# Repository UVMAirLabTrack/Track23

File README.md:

# UVM SEED 2023 Track
 
## Repository for code and setup files associated with the 2023 UVM SEED Project for an urban track for autonomous cars

## File Structure

### A. Documentation
Look in here to find the detailed instructions on how to build and run the track system. As well as more in depth information as to the system's function

- 
- 
- 
- 

### 3D modelling

Under this folder are organized locations for all the .stl files used to create the various printed elements. 

### Interactive Elements

Here you will find the Arduino IDE code files used for the ESP32 interactive element network.
Additionally Kicad format PCB's and schematics are located here.
The receiver for each interactive element utilizes the same PCB, with 4 RJ45 connectors and a single ESP32 Dev Module with 38 pins (WROOM- D or E)
The only change is which code file is flashed. 

Some previous versions utilizing pure serial connections have been left for adapability. The latest track build utilizes:

1. Stoplight
    - ESPnow_4way_4int.ino  
    - ESP_now_3Way.ino
2. Train Crossing
    - ESPNowTrain_Complete.ino
3. Sender
    - ESPnowSender.ino

With the sender node being connected via serial to the computer controlling the track, In this case a Raspberry Pi 4B 8GB model.

### CoreRaspbery 
is the ROS2 Workspace,

at present the code is designed to build into a Humble distro, however in testing the code can also be built for a Foxy distro.

### Setup Files 
contains some basic files to aid in deploying the Raspberry Pi track computer

### Car commands 
is a curated list of the terminal commands needed to operate specific functions of the Yahboom R2 car
Also contained within are some quality of life improvements to the deployment of the docker environment on the car, just some simple .sh files.

### Other Code

A series of files not directly part of the track functionality. Mostly a series of HSV decoders and Webcam Capture files 

### files not in a folder

the Dockerfiles in the main directory are intended to build a docker container to run all the ROS code, this is not intended for deployment on the PI as of this moment, instead it is intended as a complete package for the vizualizer node(s). At present, windows communication via WiFi is not functional due to additional networking constraints.

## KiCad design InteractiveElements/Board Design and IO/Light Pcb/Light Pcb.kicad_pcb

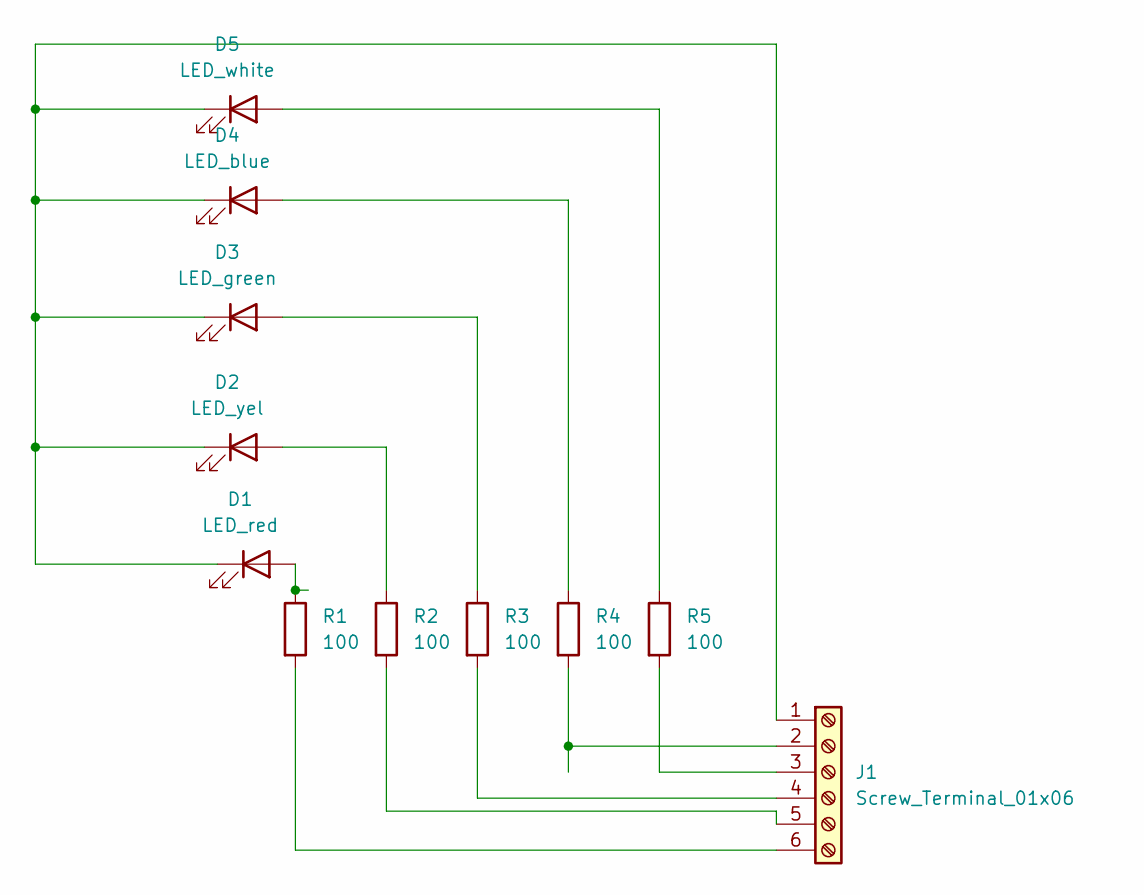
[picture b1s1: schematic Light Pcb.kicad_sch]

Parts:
D1: LED_red; LED_D5.0mm_Clear
D2: LED_yel; LED_D5.0mm_Clear
D3: LED_green; LED_D5.0mm_Clear
D4: LED_blue; LED_D5.0mm_Clear
D5: LED_white; LED_D5.0mm_Clear
J1: Screw_Terminal_01x06; PinHeader_1x06_P2.54mm_Vertical
R1, R2, R3, R4, R5: 100; R_Axial_DIN0204_L3.6mm_D1.6mm_P5.08mm_Horizontal

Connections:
unnamed: D1.2 (A), R1.1
unnamed: D1.1 (K), D2.1 (K), D3.1 (K), D4.1 (K), D5.1 (K), J1.1
unnamed: D2.2 (A), R2.1
unnamed: D3.2 (A), R3.1
unnamed: D4.2 (A), R4.1
unnamed: D5.2 (A), R5.1
unnamed: J1.2, R4.2
unnamed: J1.3, R5.2
unnamed: J1.4, R3.2
unnamed: J1.5, R2.2
unnamed: J1.6, R1.2

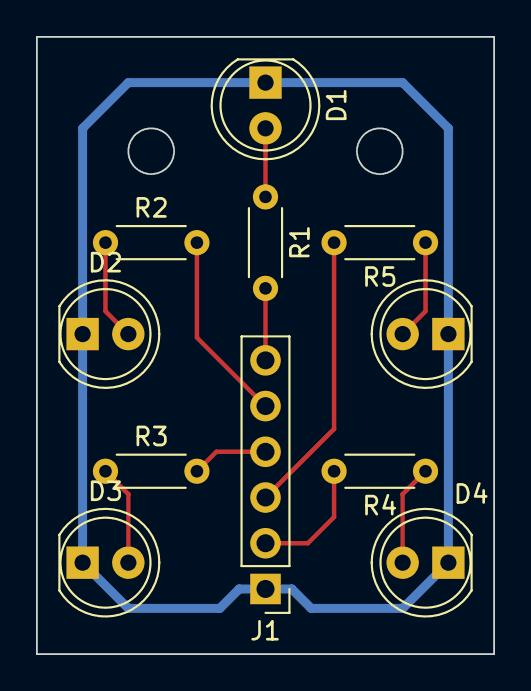
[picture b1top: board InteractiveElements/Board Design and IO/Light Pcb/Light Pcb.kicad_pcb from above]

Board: 2 copper layers, 25.4 x 34.3 mm, 11 parts (0 on the bottom side), 11 nets.

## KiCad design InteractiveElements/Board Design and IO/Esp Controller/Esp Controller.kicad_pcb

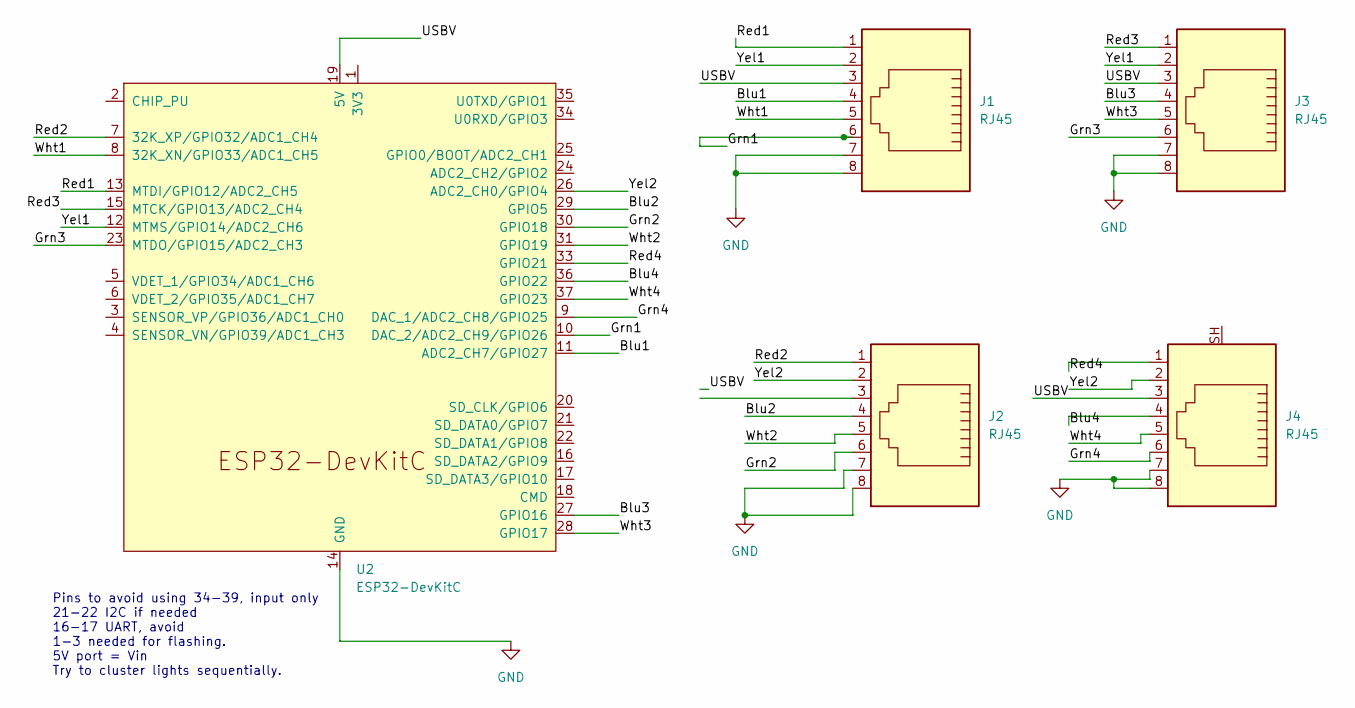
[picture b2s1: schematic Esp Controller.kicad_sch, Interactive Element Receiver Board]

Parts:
J1, J2, J3, J4: RJ45; RJ45_Amphenol_54602-x08_Horizontal
U2: ESP32-DevKitC

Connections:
/Blu1: J1.4, U2.11 (ADC2_CH7/GPIO27)
/Blu2: J2.4, U2.29 (GPIO5)
/Blu3: J3.4, U2.27 (GPIO16)
/Blu4: J4.4, U2.36 (GPIO22)
/Grn1: J1.6, U2.10 (DAC_2/ADC2_CH9/GPIO26)
/Grn2: J2.6, U2.30 (GPIO18)
/Grn3: J3.6, U2.23 (MTDO/GPIO15/ADC2_CH3)
/Grn4: J4.6, U2.9 (DAC_1/ADC2_CH8/GPIO25)
/Red1: J1.1, U2.13 (MTDI/GPIO12/ADC2_CH5)
/Red2: J2.1, U2.7 (32K_XP/GPIO32/ADC1_CH4)
/Red3: J3.1, U2.15 (MTCK/GPIO13/ADC2_CH4)
/Red4: J4.1, U2.33 (GPIO21)
/USBV: J1.3, J2.3, J3.3, J4.3, U2.19 (5V)
/Wht1: J1.5, U2.8 (32K_XN/GPIO33/ADC1_CH5)
/Wht2: J2.5, U2.31 (GPIO19)
/Wht3: J3.5, U2.28 (GPIO17)
/Wht4: J4.5, U2.37 (GPIO23)
/Yel1: J1.2, J3.2, U2.12 (MTMS/GPIO14/ADC2_CH6)
/Yel2: J2.2, J4.2, U2.26 (ADC2_CH0/GPIO4)
GND: J1.7, J1.8, J2.7, J2.8, J3.7, J3.8, J4.7, J4.8, U2.14 (GND), U2.32 (GND), U2.38 (GND)

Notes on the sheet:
Pins to avoid using 34-39, input only 21-22 I2C if needed 16-17 UART, avoid 1-3 needed for flashing. 5V port = Vin Try to cluster lights sequentially.

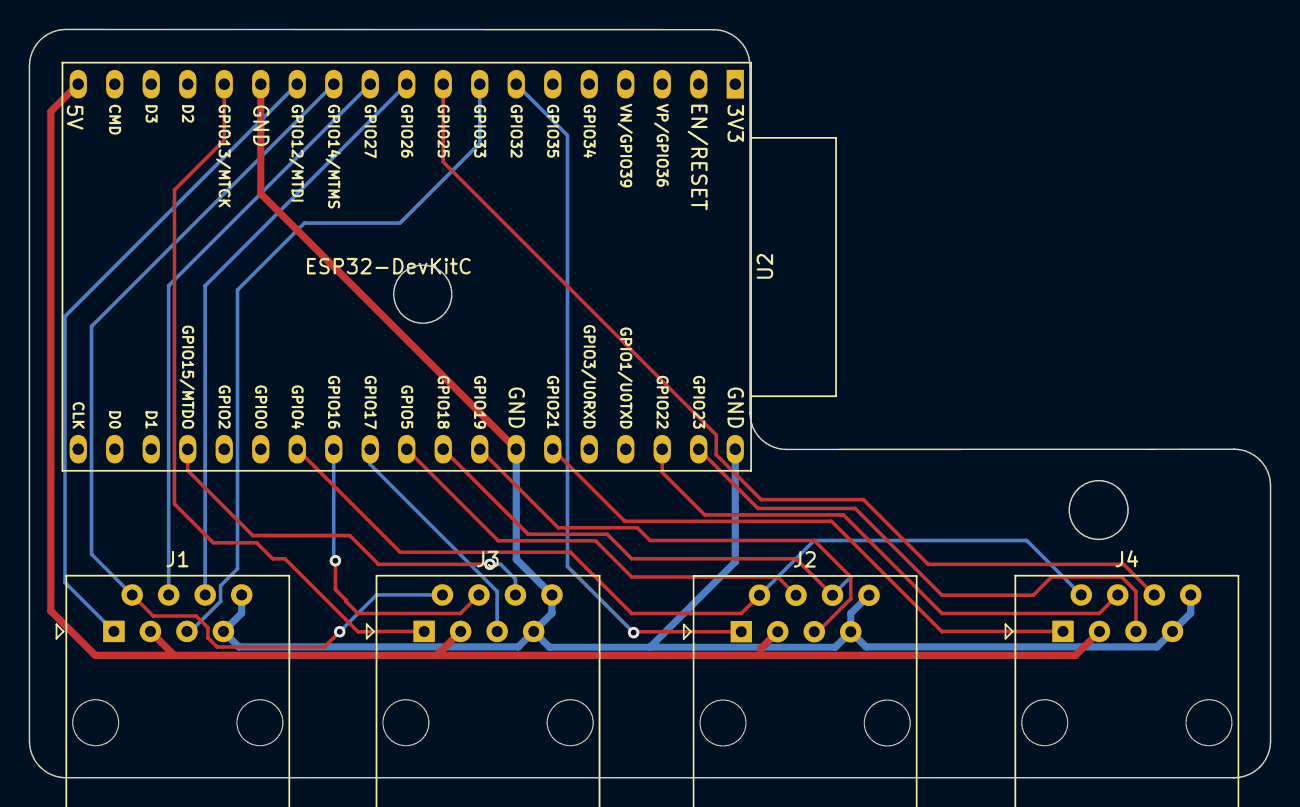
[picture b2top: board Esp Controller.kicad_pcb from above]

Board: 2 copper layers, 86.4 x 52.1 mm, 5 parts (0 on the bottom side), 20 nets.

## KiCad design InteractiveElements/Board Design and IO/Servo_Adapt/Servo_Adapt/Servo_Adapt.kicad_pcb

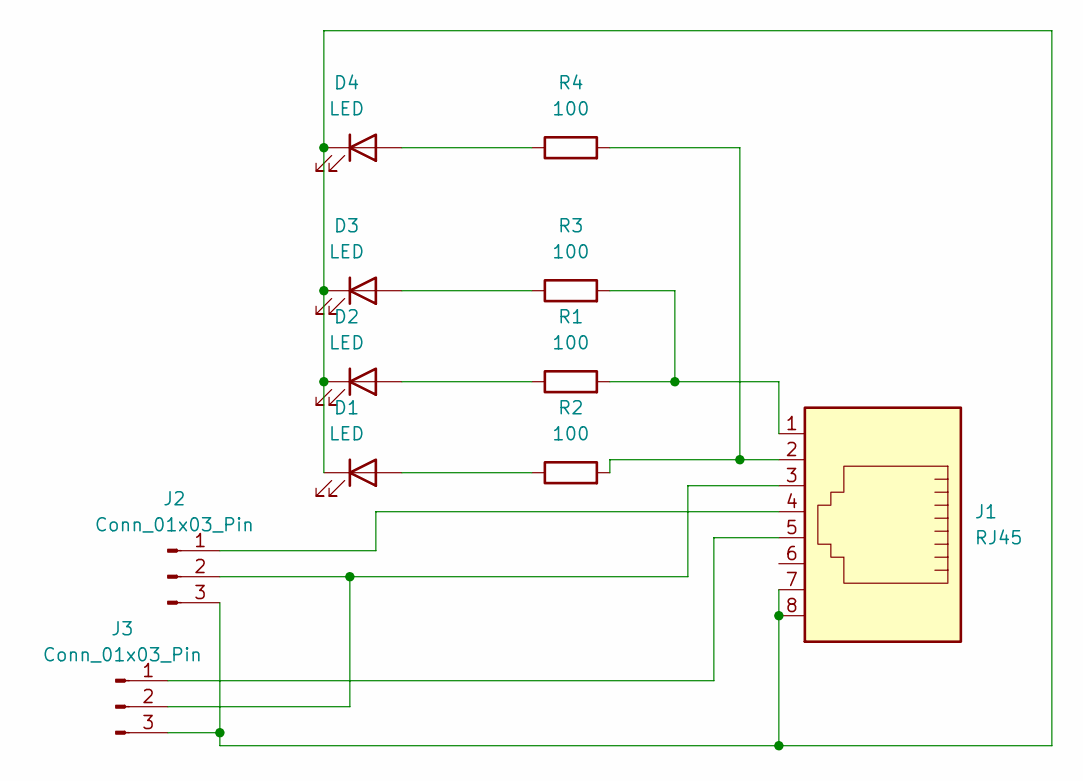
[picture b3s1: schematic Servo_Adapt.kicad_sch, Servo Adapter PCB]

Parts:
D1, D2, D3, D4: LED; LED_D5.0mm
J1: RJ45; RJ45_Amphenol_54602-x08_Horizontal
J2, J3: Conn_01x03_Pin; PinHeader_1x03_P2.54mm_Vertical
R1, R2, R3, R4: 100; R_Axial_DIN0207_L6.3mm_D2.5mm_P10.16mm_Horizontal

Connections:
unnamed: D1.2 (A), R2.1
unnamed: D1.1 (K), D2.1 (K), D3.1 (K), D4.1 (K), J1.7, J1.8, J2.3, J3.3
unnamed: D2.2 (A), R1.1
unnamed: D3.2 (A), R3.1
unnamed: D4.2 (A), R4.1
unnamed: J1.1, R1.2, R3.2
unnamed: J1.2, R2.2, R4.2
unnamed: J1.4, J2.1
unnamed: J1.3, J2.2, J3.2
unnamed: J1.5, J3.1

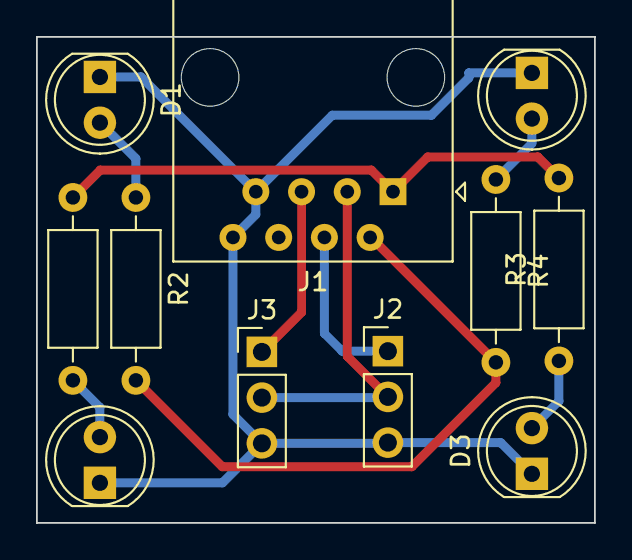
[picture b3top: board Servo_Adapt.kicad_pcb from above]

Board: 2 copper layers, 31.0 x 27.0 mm, 11 parts (0 on the bottom side), 10 nets.

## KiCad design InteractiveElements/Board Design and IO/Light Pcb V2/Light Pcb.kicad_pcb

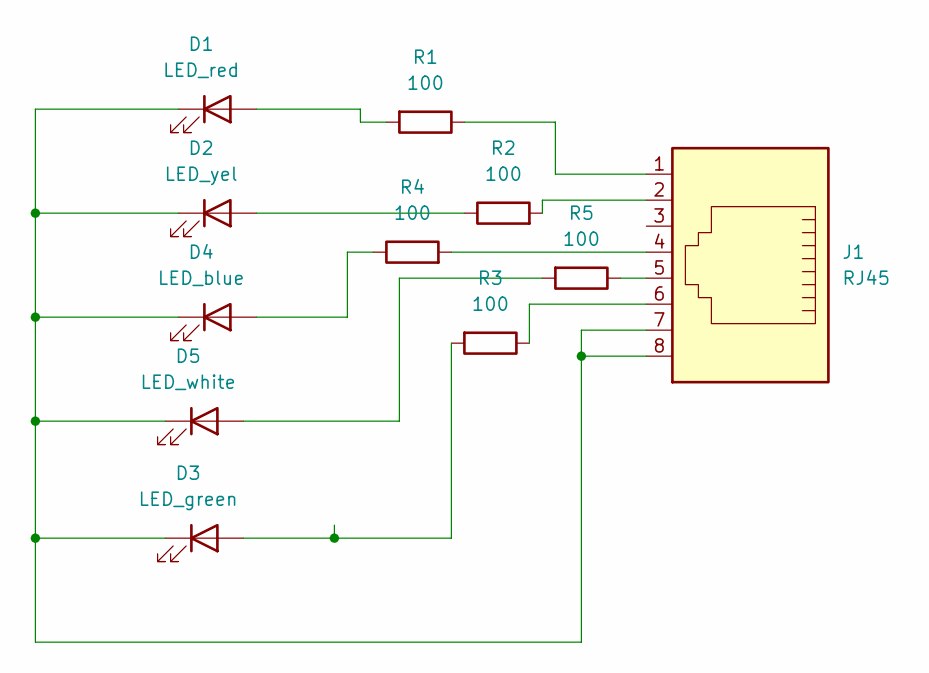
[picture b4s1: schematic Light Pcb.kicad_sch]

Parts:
D1: LED_red; LED_D5.0mm_Clear
D2: LED_yel; LED_D5.0mm_Clear
D3: LED_green; LED_D5.0mm_Clear
D4: LED_blue; LED_D5.0mm_Clear
D5: LED_white; LED_D5.0mm_Clear
J1: RJ45; RJ45_Amphenol_54602-x08_Horizontal
R1, R2, R3, R4, R5: 100; R_Axial_DIN0207_L6.3mm_D2.5mm_P7.62mm_Horizontal

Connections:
unnamed: D1.2 (A), R1.2
unnamed: D1.1 (K), D2.1 (K), D3.1 (K), D4.1 (K), D5.1 (K), J1.7, J1.8
unnamed: D2.2 (A), R2.1
unnamed: D3.2 (A), R3.2
unnamed: D4.2 (A), R4.1
unnamed: D5.2 (A), R5.2
unnamed: J1.1, R1.1
unnamed: J1.2, R2.2
unnamed: J1.4, R4.2
unnamed: J1.5, R5.1
unnamed: J1.6, R3.1

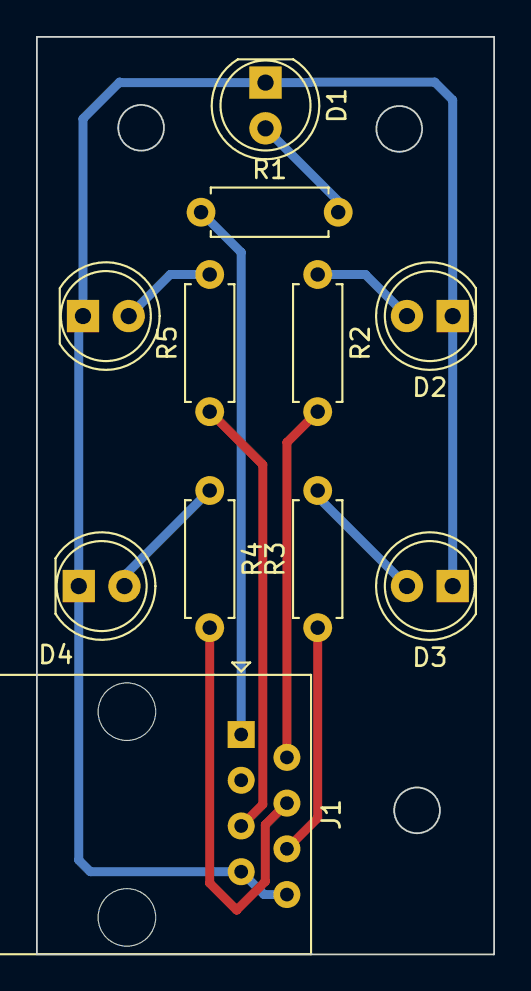
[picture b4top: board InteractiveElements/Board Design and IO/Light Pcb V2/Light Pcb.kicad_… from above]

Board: 2 copper layers, 25.4 x 51.0 mm, 11 parts (0 on the bottom side), 11 nets.

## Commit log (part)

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2024-02-19 edited cmake and package
2024-02-19 moed a folder
2024-02-19 now try a copy
2024-02-19 losta changes
2024-02-19 old lines commented
2024-02-19 edited cmake
2024-02-19 try again
2024-02-19 switched off python
2024-02-19 rclcpy oops
2024-02-19 spelling
2024-02-19 conventions
2024-02-19 new try
2024-02-19 dependencies
2024-02-19 pkg find
2024-02-19 empty
2024-02-19 new empty
2024-02-19 more empty
2024-02-19 whoops
2024-02-19 push me
2024-02-19 rename
2024-02-20 expanded to 4 int control
2024-02-20 init mods
2024-02-20 build problems
2024-02-20 changes light states
2024-02-20 modified string to int array
2024-02-20 switched from 2 to 4 int
2024-02-20 saved a copy
2024-02-20 changed to a circular test
2024-02-21 added launch file
2024-02-21 added xml line
2024-02-21 edited xml
2024-02-21 edited seup
2024-02-21 error
2024-02-21 adding rviz work
2024-02-21 edit
2024-02-21 pathing
2024-02-21 more launch files
2024-02-21 renaming problems
2024-02-21 updated text and packages
2024-02-21 refresh
2024-02-21 base_footprint not link. Agh
2024-02-21 updated world launch
2024-02-21 oops
2024-02-21 removed pynput
2024-02-21 updated track launch
2024-03-06 Updated 4 way, and some car commands
2024-03-06 Upped Serial Send to 16 ints
2024-03-06 added 16 ints to 3w, 4w, sender
2024-03-06 Moved some stuff for clarity
2024-03-07 Making a vizualizer docker
2024-03-07 moving some stuff
2024-03-07 added ignore to custom msgs, still in the works
2024-03-07 stupid colcon
2024-03-07 added some stuff
2024-03-07 trying to get x11
2024-03-07 rw nor rm
2024-03-07 added ports
2024-03-07 added more ports
2024-03-07 another attempt
2024-03-07 mods
2024-03-07 try portd
2024-03-07 Working Docker on linux
2024-03-07 powershell tweaks undone
2024-03-07 trying special message again
2024-03-07 parse problems
2024-03-07 added self
2024-03-07 try again=
2024-03-07 new pose file
2024-03-07 remoed header
2024-03-07 added itle to messages
2024-03-07 modified pose file
2024-03-08 added aruco generator
2024-03-08 cmon push this file already
2024-03-14 Preparing new message setup
2024-03-14 updated gen v2
2024-03-14 trying to make a second package
2024-03-14 new core functions package
2024-03-14 update to import
2024-03-14 .import
2024-03-14 edit setup.py
2024-03-14 dot delte
2024-03-14 edited package
2024-03-14 lets try a cmake edit
2024-03-14 tried removing cmake
2024-03-14 more edits
2024-03-14 more package edits
2024-03-14 folder layering?
2024-03-14 added a main
2024-03-14 try a rename
2024-03-14 added packages
2024-03-14 add a dummy file
2024-03-14 attempting a new method
2024-03-14 attempt 2
2024-03-14 try 3
2024-03-14 close?
2024-03-14 another try
2024-03-14 redo, maybe its a hidden problem
2024-03-14 still reading the cmake?
2024-03-14 deleted cmake
2024-03-14 dummy file
2024-03-14 finally built right,
2024-03-14 fingers crossed
2024-03-14 it works, trying an edit
2024-03-14 still working on the new msg
2024-03-14 changed timer and added multi spin
2024-03-14 added second publisher
2024-03-14 needed 2nd timer
2024-03-14 wrong message type
2024-03-14 wrong filepath
2024-03-14 trying a tester
2024-03-14 old edits
2024-03-14 changing marker
2024-03-14 switched none to empty
2024-03-14 added empty handling
2024-03-14 staging for testing
2024-03-14 edit to file
2024-03-14 edit 2
2024-03-14 another print
2024-03-14 added strip
2024-03-14 CAPS DAMNIT
2024-03-14 can you import yourself? hmm
2024-03-14 time to try 3way V2
2024-03-14 cant start with number
2024-03-14 bad index
2024-03-14 different prints
2024-03-14 more print rework
2024-03-14 one more print cleanup
2024-03-14 can you subtract pose.
2024-03-14 deleted multi_pose computation
2024-03-14 added RPY conversion
2024-03-14 quaternions suck
2024-03-14 forgot to delete import
2024-03-14 forgot a zero
2024-03-14 trying some xyz math first
2024-03-14 added zero pose indexing
2024-03-14 shifted zpm
2024-03-14 try ZPM again
2024-03-14 moed ZPM
2024-03-14 moved marker
2024-03-15 forgot a call
2024-03-15 test
2024-03-15 updated 4_way to new version
2024-03-15 update to poses
2024-03-15 another oops
2024-03-15 new light state file
2024-03-15 restored correct topics
2024-03-15 new launch files
2024-03-15 wrong exe.
2024-03-15 cleanup
2024-03-15 trying to fix hopping poses
2024-03-15 reorder
2024-03-15 stop the mad beans!!
2024-03-15 too many identical subs
2024-03-15 removed 4w
2024-03-15 gotcha
2024-03-15 trying something new
2024-03-15 copy
2024-03-15 what is going on
2024-03-15 bad spin node i think
2024-03-15 updated full launch
2024-03-15 trying to fix transform
2024-03-15 fixing launch i hope
2024-03-15 added print
2024-03-15 spare world_gen deleted
2024-03-15 push cmon
2024-03-15 edited setup glob
2024-03-15 new attempt
2024-03-17 new world testing
2024-03-17 updatd world select
2024-03-17 added train crossing i hope
2024-03-17 multi init
2024-03-17 new location, and reducing some logging
2024-03-17 one too many Values
2024-03-17 cant see the train, Why?
2024-03-17 new location angles, and corrected state.
2024-03-17 try this update
2024-03-17 copied from world_gen for testing
2024-03-17 quaternion converter added
2024-03-17 split out eulers
2024-03-17 bad indexing
2024-03-17 initialize with values
2024-03-17 quaternion
2024-03-17 try quaternion again
2024-03-17 index update
2024-03-17 more bad indexing
2024-03-17 launch renames
2024-03-17 added new world configs
2024-03-17 delete
2024-03-17 touchup
2024-03-17 update launch
2024-03-17 idiot
2024-03-17 edited dockerfile
2024-03-17 tweaking dockerfile
2024-03-18 docker order problems
2024-03-18 source then build
2024-03-18 root not home
2024-03-18 modded dockerfile
2024-03-18 brought some linux files over
2024-03-18 one more docker update
2024-03-18 idiot pathing again
2024-03-18 docker edit
2024-03-18 changed the serial output for full monitoring with any connected endpoint
2024-03-18 adding a webcam capture python file
2024-03-18 webcam file operational success.
2024-03-18 minor tweaks
2024-03-19 added webcam cap
2024-03-19 new dockerfile for the cars
2024-03-20 new file
2024-03-20 old version recommit
2024-03-21 added banded hsv_v2
2024-03-21 edits
2024-03-21 edit2
2024-03-21 bandwidth slider final version
2024-03-21 think that does it
2024-03-21 min max ready
2024-03-21 sliders added
2024-03-21 added box to have a preset HSV
2024-03-22 changes to line follower.
2024-03-27 added the stop sign publisher
2024-03-27 mieed a file
2024-03-27 updated to add a sign
2024-03-27 orientation, not position...
2024-03-27 cleanup and adding multi shift
2024-03-27 testing
2024-03-27 added Z rotation to other setups
2024-03-27 cleaned up train marker
2024-03-27 tweaks
2024-03-27 yield signs added
2024-03-27 built, and added an animal publisher
2024-03-28 newest dockerfiles added
2024-03-28 added dragon
2024-03-29 added 3d modelling folder
2024-03-29 small oval added
2024-03-29 testing the oval.
2024-03-29 deleted a line
2024-03-29 small change
2024-03-29 inverted x and y
2024-03-29 negative signs
2024-03-29 trying again
2024-03-29 is it doubling size?
2024-03-29 editd
2024-03-29 bad math maybe?
2024-03-29 x+dx sucks
2024-03-29 new light
2024-03-29 corrections
2024-03-29 more
2024-03-29 dragon pose
2024-03-29 print added
2024-04-05 corrected marker loc. IT WORKS!!!
2024-04-05 old was working, new adds reset and some stuff in mesh pub esp_Serial had wrong topic for train
2024-04-09 Odom, not pose
2024-04-09 quaternion math problems
2024-04-09 adding a reset publisher hopefully
2024-04-09 5 second reset
2024-04-09 some msg updates/
2024-04-09 print helps
2024-04-09 updating the odometry handle.
2024-04-09 more update
2024-04-09 close
2024-04-09 msg.data
2024-04-09 debug print
2024-04-09 wrong order?
2024-04-09 once again
2024-04-09 new prints
2024-04-09 updated formula
2024-04-10 funny math
2024-04-10 new publisher with pose stripping
2024-04-10 new worlds
2024-04-10 more news
2024-04-10 last new worlds
2024-04-11 new woelds
2024-04-11 car box added
2024-04-11 debug work
2024-04-12 forgotten commit
2024-04-12 I think this does it
2024-04-12 added pub_time parameter
2024-04-12 new patterns
2024-04-12 new world work
2024-04-12 new odometry
2024-04-12 tuples...
2024-04-12 floats
2024-04-12 print statements for testing
2024-04-13 update to quaternion
2024-04-13 more tweaks
2024-04-13 moved a ref
2024-04-13 adding an angular shift
2024-04-13 xy rotation
2024-04-13 now to get v2 running
2024-04-13 map parser ready?
2024-04-13 maybe?
2024-04-13 box is now green
2024-04-13 added a odometry reader
2024-04-15 new markers?
2024-04-15 added images
2024-04-15 more images
2024-04-17 add image
2024-04-18 simplified states, hoping this is the end of odom
2024-04-18 added start marker
2024-04-18 still updating odom
2024-04-18 again
2024-04-18 last try2
2024-04-24 updated lights
2024-04-26 stuff
2024-04-26 video viewer
2024-04-27 updated schematic
2024-04-27 file move
2024-04-27 moved up one layer
2024-04-27 reorganize
2024-04-27 Added Yolo Package
2024-09-05 last push
